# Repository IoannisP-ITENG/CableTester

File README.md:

<div align="center">

# CableTester

<br/>

USB type-C and UTP cable tester designed in faebryk

</div>

## About

This is a simple USB type-C and UTP cable continuity tester. It lights up the LED corresponding to the strand it is testing when there is an electrical connection. The tester is powered with 5V via the PD compliant USB type-C connector.

This project is build with the open-source EDA [faebryk](https://github.com/faebryk/faebryk).

## What can you do with this project?

This project is usefull as a simple cable tester for UTP and USB type-C cables, however it is very easy to add additional connectors for different cable types due to faebryk.

The purpose of this project was mainly to showcase the funcionality of faebryk. The Cable tester is the very first PCBA manufactured from a faebryk design!

### Example

<details>
  <summary>An example of the power of faebryk for PCB design</summary>

</br>

Auto placing components.

```bash
# Generate the netlist with faebryk
python ./source/faebryk/main.py
INFO:__main__:Backup old netlist at ./source/kicad/main/main.net.bak
INFO:__main__:Writing Experiment netlist to ./source/kicad/main/main.net
INFO:__main__:Opening kicad to import new netlist
Import the netlist at ./source/kicad/main/main.net. Press 'Update 
PCB'. Place the components, save the file and exit kicad.

# Let faebryk auto-place your component in a parametric way
INFO:__main__:Writing pcbfile ./source/kicad/main/main.kicad_pcb
```

After importing the generated netlist into KiCad, the layout looks like this:

Let faebryk do the parametric auto placing by using transform functions and coordinates:

```python
# component, rotation
layout_rotation_degrees: List[Tuple[Component, int]] = [
    (pr, 270),
    (mos, 180),
    (clr, 270),
    (led, 0),
]

# left, up, right, down
component_clearances_mm = {
    LED_FP: (2.25, 1, 2, 1),
    RESISTOR_FP: (1, 0.5, 1, 0.5),
    MOSFET_FPS[0]: (2, 3.25, 2, 3.25),
    MOSFET_FPS[1]: (2, 3.25, 2, 3.25),
}
```

And you will get a parametrized PCB layout:

</details>

## Working with the source files

See [here](./docs/development.md) for the instructions on how to install and edit this project.

## Building

If you want to build the physical output of this project you can find the build instructions [here](./docs/build_instructions.md).

## Contributing

If you want to share your alterations, improvements, or add bugfixes to this project, please take a look at the [contributing guidelines](./docs/CONTRIBUTING.md).

## Community Support

Community support is provided via Discord; see the Resources below for details.

### Resources

- Source Code: [Github](https://github.com/IoannisP-ITENG/CableTester)
- Chat: Real-time chat happens in faebryk's Discord Server (chit-chat room for now). Use this Discord [Invite](https://discord.gg/95jYuPmnUW) to register
- Issues: [Issues](https://github.com/IoannisP-ITENG/CableTester/issues)

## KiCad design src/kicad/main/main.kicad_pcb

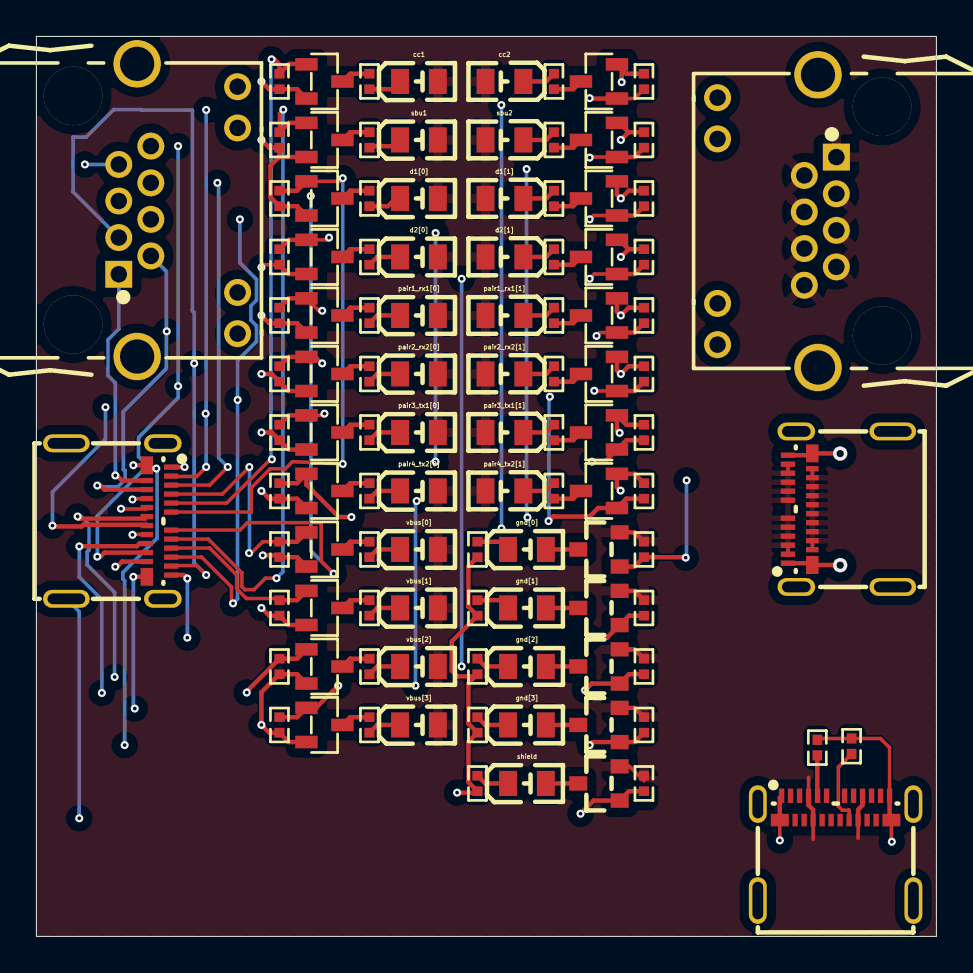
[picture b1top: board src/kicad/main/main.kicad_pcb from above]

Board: 4 copper layers, 50.0 x 50.0 mm, 107 parts (0 on the bottom side), 79 nets.

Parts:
*.psu.configuration_resistors[0][Resistor:5.1kΩ], *.psu.configuration_resistors[1][Resistor:5.1kΩ]: 5.1kΩ; R0402
*.psu.usb[USB_Type_C_Receptacle_24_pin:x], *.tester.usb_c[0][USB_Type_C_Receptacle_24_pin:x], *.tester.usb_c[1][USB_Type_C_Receptacle_24_pin:x]: x; USB-C-SMD_TYPE-C-USB-18
*.tester.cc1.indicator.led.current_limiting_resistor[Resistor:1.0kΩ], *.tester.cc2.indicator.led.current_limiting_resistor[Resistor:1.0kΩ], *.tester.d1[0].indicator.led.current_limiting_resistor[Resistor:1.0kΩ], *.tester.d1[1].indicator.led.current_limiting_resistor[Resistor:1.0kΩ], *.tester.d2[0].indicator.led.current_limiting_resistor[Resistor:1.0kΩ], *.tester.d2[1].indicator.led.current_limiting_resistor[Resistor:1.0kΩ], *.tester.gnd[0].indicator.led.current_limiting_resistor[Resistor:1.0kΩ], *.tester.gnd[1].indicator.led.current_limiting_resistor[Resistor:1.0kΩ], *.tester.gnd[2].indicator.led.current_limiting_resistor[Resistor:1.0kΩ], *.tester.gnd[3].indicator.led.current_limiting_resistor[Resistor:1.0kΩ], *.tester.pair1_rx1[0].indicator.led.current_limiting_resistor[Resistor:1.0kΩ], *.tester.pair1_rx1[1].indicator.led.current_limiting_resistor[Resistor:1.0kΩ], *.tester.pair2_rx2[0].indicator.led.current_limiting_resistor[Resistor:1.0kΩ], *.tester.pair2_rx2[1].indicator.led.current_limiting_resistor[Resistor:1.0kΩ], *.tester.pair3_tx1[0].indicator.led.current_limiting_resistor[Resistor:1.0kΩ], *.tester.pair3_tx1[1].indicator.led.current_limiting_resistor[Resistor:1.0kΩ], *.tester.pair4_tx2[0].indicator.led.current_limiting_resistor[Resistor:1.0kΩ], *.tester.pair4_tx2[1].indicator.led.current_limiting_resistor[Resistor:1.0kΩ], *.tester.sbu1.indicator.led.current_limiting_resistor[Resistor:1.0kΩ], *.tester.sbu2.indicator.led.current_limiting_resistor[Resistor:1.0kΩ], *.tester.shield.indicator.led.current_limiting_resistor[Resistor:1.0kΩ], *.tester.vbus[0].indicator.led.current_limiting_resistor[Resistor:1.0kΩ], *.tester.vbus[1].indicator.led.current_limiting_resistor[Resistor:1.0kΩ], *.tester.vbus[2].indicator.led.current_limiting_resistor[Resistor:1.0kΩ], *.tester.vbus[3].indicator.led.current_limiting_resistor[Resistor:1.0kΩ]: 1.0kΩ; R0402
*.tester.cc1.indicator.led.led[LED:D], *.tester.cc2.indicator.led.led[LED:D], *.tester.d1[0].indicator.led.led[LED:D], *.tester.d1[1].indicator.led.led[LED:D], *.tester.d2[0].indicator.led.led[LED:D], *.tester.d2[1].indicator.led.led[LED:D], *.tester.gnd[0].indicator.led.led[LED:D], *.tester.gnd[1].indicator.led.led[LED:D], *.tester.gnd[2].indicator.led.led[LED:D], *.tester.gnd[3].indicator.led.led[LED:D], *.tester.pair1_rx1[0].indicator.led.led[LED:D], *.tester.pair1_rx1[1].indicator.led.led[LED:D], *.tester.pair2_rx2[0].indicator.led.led[LED:D], *.tester.pair2_rx2[1].indicator.led.led[LED:D], *.tester.pair3_tx1[0].indicator.led.led[LED:D], *.tester.pair3_tx1[1].indicator.led.led[LED:D], *.tester.pair4_tx2[0].indicator.led.led[LED:D], *.tester.pair4_tx2[1].indicator.led.led[LED:D], *.tester.sbu1.indicator.led.led[LED:D], *.tester.sbu2.indicator.led.led[LED:D], *.tester.shield.indicator.led.led[LED:D], *.tester.vbus[0].indicator.led.led[LED:D], *.tester.vbus[1].indicator.led.led[LED:D], *.tester.vbus[2].indicator.led.led[LED:D], *.tester.vbus[3].indicator.led.led[LED:D]: D; LED0805-R-RD
*.tester.cc1.indicator.power_switch.mosfet[MOSFET:Q], *.tester.cc2.indicator.power_switch.mosfet[MOSFET:Q], *.tester.d1[0].indicator.power_switch.mosfet[MOSFET:Q], *.tester.d1[1].indicator.power_switch.mosfet[MOSFET:Q], *.tester.d2[0].indicator.power_switch.mosfet[MOSFET:Q], *.tester.d2[1].indicator.power_switch.mosfet[MOSFET:Q], *.tester.pair1_rx1[0].indicator.power_switch.mosfet[MOSFET:Q], *.tester.pair1_rx1[1].indicator.power_switch.mosfet[MOSFET:Q], *.tester.pair2_rx2[0].indicator.power_switch.mosfet[MOSFET:Q], *.tester.pair2_rx2[1].indicator.power_switch.mosfet[MOSFET:Q], *.tester.pair3_tx1[0].indicator.power_switch.mosfet[MOSFET:Q], *.tester.pair3_tx1[1].indicator.power_switch.mosfet[MOSFET:Q], *.tester.pair4_tx2[0].indicator.power_switch.mosfet[MOSFET:Q], *.tester.pair4_tx2[1].indicator.power_switch.mosfet[MOSFET:Q], *.tester.sbu1.indicator.power_switch.mosfet[MOSFET:Q], *.tester.sbu2.indicator.power_switch.mosfet[MOSFET:Q], *.tester.vbus[0].indicator.power_switch.mosfet[MOSFET:Q], *.tester.vbus[1].indicator.power_switch.mosfet[MOSFET:Q], *.tester.vbus[2].indicator.power_switch.mosfet[MOSFET:Q], *.tester.vbus[3].indicator.power_switch.mosfet[MOSFET:Q]: Q; SOT-23-3_L2.9-W1.3-P1.90-LS2.4-BR
*.tester.cc1.indicator.power_switch.pull_resistor[Resistor:100.0kΩ], *.tester.cc2.indicator.power_switch.pull_resistor[Resistor:100.0kΩ], *.tester.d1[0].indicator.power_switch.pull_resistor[Resistor:100.0kΩ], *.tester.d1[1].indicator.power_switch.pull_resistor[Resistor:100.0kΩ], *.tester.d2[0].indicator.power_switch.pull_resistor[Resistor:100.0kΩ], *.tester.d2[1].indicator.power_switch.pull_resistor[Resistor:100.0kΩ], *.tester.gnd[0].indicator.power_switch.pull_resistor[Resistor:100.0kΩ], *.tester.gnd[1].indicator.power_switch.pull_resistor[Resistor:100.0kΩ], *.tester.gnd[2].indicator.power_switch.pull_resistor[Resistor:100.0kΩ], *.tester.gnd[3].indicator.power_switch.pull_resistor[Resistor:100.0kΩ], *.tester.pair1_rx1[0].indicator.power_switch.pull_resistor[Resistor:100.0kΩ], *.tester.pair1_rx1[1].indicator.power_switch.pull_resistor[Resistor:100.0kΩ], *.tester.pair2_rx2[0].indicator.power_switch.pull_resistor[Resistor:100.0kΩ], *.tester.pair2_rx2[1].indicator.power_switch.pull_resistor[Resistor:100.0kΩ], *.tester.pair3_tx1[0].indicator.power_switch.pull_resistor[Resistor:100.0kΩ], *.tester.pair3_tx1[1].indicator.power_switch.pull_resistor[Resistor:100.0kΩ], *.tester.pair4_tx2[0].indicator.power_switch.pull_resistor[Resistor:100.0kΩ], *.tester.pair4_tx2[1].indicator.power_switch.pull_resistor[Resistor:100.0kΩ], *.tester.sbu1.indicator.power_switch.pull_resistor[Resistor:100.0kΩ], *.tester.sbu2.indicator.power_switch.pull_resistor[Resistor:100.0kΩ], *.tester.shield.indicator.power_switch.pull_resistor[Resistor:100.0kΩ], *.tester.vbus[0].indicator.power_switch.pull_resistor[Resistor:100.0kΩ], *.tester.vbus[1].indicator.power_switch.pull_resistor[Resistor:100.0kΩ], *.tester.vbus[2].indicator.power_switch.pull_resistor[Resistor:100.0kΩ], *.tester.vbus[3].indicator.power_switch.pull_resistor[Resistor:100.0kΩ]: 100.0kΩ; R0402
*.tester.gnd[0].indicator.power_switch.mosfet[MOSFET:Q], *.tester.gnd[1].indicator.power_switch.mosfet[MOSFET:Q], *.tester.gnd[2].indicator.power_switch.mosfet[MOSFET:Q], *.tester.gnd[3].indicator.power_switch.mosfet[MOSFET:Q], *.tester.shield.indicator.power_switch.mosfet[MOSFET:Q]: Q; SOT-23_L2.9-W1.3-P1.90-LS2.4-BR
*.tester.rj45[0][RJ45_Receptacle:x], *.tester.rj45[1][RJ45_Receptacle:x]: x; RJ45-TH_B-1-1

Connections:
*.psu.usb[USB_Type_C_Receptacle_24_pin:x]-psu.configuration_resistors[0][Resist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: *.psu.configuration_resistors[0][Resist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.1, *.psu.usb[USB_Type_C_Receptacle_24_pin: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.A5
*.psu.usb[USB_Type_C_Receptacle_24_pin:x]-psu.configuration_resistors[1][Resist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: *.psu.configuration_resistors[1][Resist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.1, *.psu.usb[USB_Type_C_Receptacle_24_pin: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.B5
*.tester.cc1.indicator.led.current_limiting_resistor[Resistor:1.0kΩ]-*.tester.c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: *.tester.cc1.indicator.led.current_limi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.2, *.tester.cc1.indicator.led.led[LED:D].2
*.tester.cc1.indicator.power_switch[PowerSwitch:virt]:5-*.tester.cc1.indicator.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: *.tester.cc1.indicator.led.current_limi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.1, *.tester.cc1.indicator.power_switch.mos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.3
*.tester.cc1.indicator[LEDIndicator:virt]-*.tester.cc1.indicator.power_switch[P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: *.tester.cc1.indicator.power_switch.mos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.1, *.tester.cc1.indicator.power_switch.pul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.1, *.tester.usb_c[1][USB_Type_C_Receptacle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.A5
*.tester.cc2.indicator.led.led[LED:D]-*.tester.cc2.indicator.led.current_limiti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: *.tester.cc2.indicator.led.current_limi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.2, *.tester.cc2.indicator.led.led[LED:D].2
*.tester.cc2.indicator.power_switch[PowerSwitch:virt]-*.tester.cc2.indicator[LE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: *.tester.cc2.indicator.power_switch.mos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.1, *.tester.cc2.indicator.power_switch.pul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.1, *.tester.usb_c[1][USB_Type_C_Receptacle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.B5
*.tester.cc2.indicator.power_switch[PowerSwitch:virt]:5-*.tester.cc2.indicator.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: *.tester.cc2.indicator.led.current_limi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.1, *.tester.cc2.indicator.power_switch.mos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.3
*.tester.d1[0].indicator.led.current_limiting_resistor[Resistor:1.0kΩ]-*.tester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: *.tester.d1[0].indicator.led.current_li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.2, *.tester.d1[0].indicator.led.led[LED:D].2
*.tester.d1[0].indicator.led[PoweredLED:virt]:2-*.tester.d1[0].indicator.power_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: *.tester.d1[0].indicator.led.current_li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.1, *.tester.d1[0].indicator.power_switch.m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.3
*.tester.d1[0].indicator[LEDIndicator:virt]-*.tester.d1[0].indicator.power_swit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: *.tester.d1[0].indicator.power_switch.m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.1, *.tester.d1[0].indicator.power_switch.p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.1, *.tester.usb_c[1][USB_Type_C_Receptacle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.A6
*.tester.d1[1].indicator.led.led[LED:D]-*.tester.d1[1].indicator.led.current_li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: *.tester.d1[1].indicator.led.current_li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.2, *.tester.d1[1].indicator.led.led[LED:D].2
*.tester.d1[1].indicator.power_switch[PowerSwitch:virt]-*.tester.d1[1][Pair*.te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: *.tester.d1[1].indicator.power_switch.m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.1, *.tester.d1[1].indicator.power_switch.p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.1, *.tester.usb_c[1][USB_Type_C_Receptacle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.A7
*.tester.d1[1].indicator.power_switch[PowerSwitch:virt]:5-*.tester.d1[1].indica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: *.tester.d1[1].indicator.led.current_li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.1, *.tester.d1[1].indicator.power_switch.m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.3
*.tester.d2[0].indicator.led.current_limiting_resistor[Resistor:1.0kΩ]-*.tester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: *.tester.d2[0].indicator.led.current_li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.2, *.tester.d2[0].indicator.led.led[LED:D].2
*.tester.d2[0].indicator.power_switch[PowerSwitch:virt]:5-*.tester.d2[0].indica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: *.tester.d2[0].indicator.led.current_li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.1, *.tester.d2[0].indicator.power_switch.m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.3
*.tester.d2[0][Pair*.tester:virt]:4-*.tester.d2[0].indicator.power_switch[Power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: *.tester.d2[0].indicator.power_switch.m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.1, *.tester.d2[0].indicator.power_switch.p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.1, *.tester.usb_c[1][USB_Type_C_Receptacle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.B6
*.tester.d2[1].indicator.led.current_limiting_resistor[Resistor:1.0kΩ]-*.tester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: *.tester.d2[1].indicator.led.current_li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.2, *.tester.d2[1].indicator.led.led[LED:D].2
*.tester.d2[1].indicator.power_switch[PowerSwitch:virt]:5-*.tester.d2[1].indica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: *.tester.d2[1].indicator.led.current_li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.1, *.tester.d2[1].indicator.power_switch.m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.3
*.tester.d2[1][Pair*.tester:virt]:4-*.tester.d2[1].indicator[LEDIndicator:virt]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: *.tester.d2[1].indicator.power_switch.m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.1, *.tester.d2[1].indicator.power_switch.p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.1, *.tester.usb_c[1][USB_Type_C_Receptacle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.B7
*.tester.gnd[0].indicator.led.led[LED:D]-*.tester.gnd[0].indicator.led.current_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: *.tester.gnd[0].indicator.led.current_l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.2, *.tester.gnd[0].indicator.led.led[LED:D].2
*.tester.gnd[0].indicator.power_switch[PowerSwitch:virt]-*.tester.gnd[0].indica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: *.tester.gnd[0].indicator.power_switch.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.1, *.tester.gnd[0].indicator.power_switch.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.1, *.tester.usb_c[1][USB_Type_C_Receptacle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.A1
*.tester.gnd[0].indicator.power_switch[PowerSwitch:virt]:4-*.tester.gnd[0].indi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: *.tester.gnd[0].indicator.led.led[LED:D].1, *.tester.gnd[0].indicator.power_switch.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.3
*.tester.gnd[1].indicator.led.led[LED:D]-*.tester.gnd[1].indicator.led.current_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: *.tester.gnd[1].indicator.led.current_l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.2, *.tester.gnd[1].indicator.led.led[LED:D].2
*.tester.gnd[1].indicator.power_switch[PowerSwitch:virt]:4-*.tester.gnd[1].indi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: *.tester.gnd[1].indicator.led.led[LED:D].1, *.tester.gnd[1].indicator.power_switch.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.3
*.tester.gnd[1][Pair*.tester:virt]:4-*.tester.gnd[1].indicator.power_switch[Pow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: *.tester.gnd[1].indicator.power_switch.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.1, *.tester.gnd[1].indicator.power_switch.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.1, *.tester.usb_c[1][USB_Type_C_Receptacle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.A12
*.tester.gnd[2].indicator.led.led[LED:D]-*.tester.gnd[2].indicator.led.current_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: *.tester.gnd[2].indicator.led.current_l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.2, *.tester.gnd[2].indicator.led.led[LED:D].2
*.tester.gnd[2].indicator.led[PoweredLED:virt]-*.tester.gnd[2].indicator.power_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: *.tester.gnd[2].indicator.led.led[LED:D].1, *.tester.gnd[2].indicator.power_switch.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.3
*.tester.gnd[2][Pair*.tester:virt]:4-*.tester.gnd[2].indicator[LEDIndicator:vir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: *.tester.gnd[2].indicator.power_switch.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.1, *.tester.gnd[2].indicator.power_switch.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.1, *.tester.usb_c[1][USB_Type_C_Receptacle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.B1
*.tester.gnd[3].indicator.led.led[LED:D]-*.tester.gnd[3].indicator.led.current_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: *.tester.gnd[3].indicator.led.current_l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.2, *.tester.gnd[3].indicator.led.led[LED:D].2
*.tester.gnd[3].indicator.led[PoweredLED:virt]-*.tester.gnd[3].indicator.power_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: *.tester.gnd[3].indicator.led.led[LED:D].1, *.tester.gnd[3].indicator.power_switch.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.3
*.tester.gnd[3][Pair*.tester:virt]:4-*.tester.gnd[3].indicator[LEDIndicator:vir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: *.tester.gnd[3].indicator.power_switch.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.1, *.tester.gnd[3].indicator.power_switch.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.1, *.tester.usb_c[1][USB_Type_C_Receptacle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.B12
*.tester.pair1_rx1[0].indicator.led.led[LED:D]-*.tester.pair1_rx1[0].indicator.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: *.tester.pair1_rx1[0].indicator.led.cur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.2, *.tester.pair1_rx1[0].indicator.led.led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.2
*.tester.pair1_rx1[0].indicator.led[PoweredLED:virt]:2-*.tester.pair1_rx1[0].in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: *.tester.pair1_rx1[0].indicator.led.cur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.1, *.tester.pair1_rx1[0].indicator.power_s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.3
*.tester.pair1_rx1[0][Pair*.tester:virt]:4-*.tester.pair1_rx1[0].indicator.powe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: *.tester.pair1_rx1[0].indicator.power_s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.1, *.tester.pair1_rx1[0].indicator.power_s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.1, *.tester.rj45[1][RJ45_Receptacle:x].1, *.tester.usb_c[1][USB_Type_C_Receptacle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.B11
*.tester.pair1_rx1[1].indicator.led.current_limiting_resistor[Resistor:1.0kΩ]-*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: *.tester.pair1_rx1[1].indicator.led.cur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.2, *.tester.pair1_rx1[1].indicator.led.led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.2
*.tester.pair1_rx1[1].indicator.led[PoweredLED:virt]-*.tester.d2[1].indicator.p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: *.psu.usb[USB_Type_C_Receptacle_24_pin: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.A4, *.psu.usb[USB_Type_C_Receptacle_24_pin: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.A9, *.psu.usb[USB_Type_C_Receptacle_24_pin: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.B4, *.psu.usb[USB_Type_C_Receptacle_24_pin: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.B9, *.tester.cc1.indicator.led.led[LED:D].1, *.tester.cc2.indicator.led.led[LED:D].1, *.tester.d1[0].indicator.led.led[LED:D].1, *.tester.d1[1].indicator.led.led[LED:D].1, *.tester.d2[0].indicator.led.led[LED:D].1, *.tester.d2[1].indicator.led.led[LED:D].1, *.tester.gnd[0].indicator.power_switch.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.2, *.tester.gnd[0].indicator.power_switch.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.2, *.tester.gnd[1].indicator.power_switch.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.2, *.tester.gnd[1].indicator.power_switch.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.2, *.tester.gnd[2].indicator.power_switch.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.2, *.tester.gnd[2].indicator.power_switch.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.2, *.tester.gnd[3].indicator.power_switch.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.2, *.tester.gnd[3].indicator.power_switch.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.2, *.tester.pair1_rx1[0].indicator.led.led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.1, *.tester.pair1_rx1[1].indicator.led.led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.1, *.tester.pair2_rx2[0].indicator.led.led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.1, *.tester.pair2_rx2[1].indicator.led.led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.1, *.tester.pair3_tx1[0].indicator.led.led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.1, *.tester.pair3_tx1[1].indicator.led.led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.1, *.tester.pair4_tx2[0].indicator.led.led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.1, *.tester.pair4_tx2[1].indicator.led.led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.1, *.tester.rj45[0][RJ45_Receptacle:x].1, *.tester.rj45[0][RJ45_Receptacle:x].2, *.tester.rj45[0][RJ45_Receptacle:x].3, *.tester.rj45[0][RJ45_Receptacle:x].4, *.tester.rj45[0][RJ45_Receptacle:x].5, *.tester.rj45[0][RJ45_Receptacle:x].6, *.tester.rj45[0][RJ45_Receptacle:x].7, *.tester.rj45[0][RJ45_Receptacle:x].8, *.tester.sbu1.indicator.led.led[LED:D].1, *.tester.sbu2.indicator.led.led[LED:D].1, *.tester.shield.indicator.power_switch.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.2, *.tester.shield.indicator.power_switch.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.2, *.tester.usb_c[0][USB_Type_C_Receptacle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.A2, *.tester.usb_c[0][USB_Type_C_Receptacle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.A3, *.tester.usb_c[0][USB_Type_C_Receptacle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.A4, *.tester.usb_c[0][USB_Type_C_Receptacle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.A5, *.tester.usb_c[0][USB_Type_C_Receptacle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.A6, *.tester.usb_c[0][USB_Type_C_Receptacle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.A7, *.tester.usb_c[0][USB_Type_C_Receptacle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.A8, *.tester.usb_c[0][USB_Type_C_Receptacle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.A9, *.tester.usb_c[0][USB_Type_C_Receptacle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.A10, *.tester.usb_c[0][USB_Type_C_Receptacle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.A11, *.tester.usb_c[0][USB_Type_C_Receptacle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.B2, *.tester.usb_c[0][USB_Type_C_Receptacle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.B3, *.tester.usb_c[0][USB_Type_C_Receptacle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.B4, *.tester.usb_c[0][USB_Type_C_Receptacle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.B5, *.tester.usb_c[0][USB_Type_C_Receptacle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.B6, *.tester.usb_c[0][USB_Type_C_Receptacle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.B7, *.tester.usb_c[0][USB_Type_C_Receptacle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.B8, *.tester.usb_c[0][USB_Type_C_Receptacle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.B9, *.tester.usb_c[0][USB_Type_C_Receptacle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.B10, *.tester.usb_c[0][USB_Type_C_Receptacle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.B11, *.tester.vbus[0].indicator.led.led[LED: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.1, *.tester.vbus[1].indicator.led.led[LED: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.1, *.tester.vbus[2].indicator.led.led[LED: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.1, *.tester.vbus[3].indicator.led.led[LED: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.1
*.tester.pair1_rx1[1].indicator.power_switch[PowerSwitch:virt]:5-*.tester.pair1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: *.tester.pair1_rx1[1].indicator.led.cur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.1, *.tester.pair1_rx1[1].indicator.power_s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.3
*.tester.pair1_rx1[1][Pair*.tester:virt]:4-*.tester.pair1_rx1[1].indicator[LEDI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: *.tester.pair1_rx1[1].indicator.power_s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.1, *.tester.pair1_rx1[1].indicator.power_s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.1, *.tester.rj45[1][RJ45_Receptacle:x].2, *.tester.usb_c[1][USB_Type_C_Receptacle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.B10
*.tester.pair2_rx2[0].indicator.led.led[LED:D]-*.tester.pair2_rx2[0].indicator.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: *.tester.pair2_rx2[0].indicator.led.cur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.2, *.tester.pair2_rx2[0].indicator.led.led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.2
*.tester.pair2_rx2[0].indicator.power_switch[PowerSwitch:virt]:5-*.tester.pair2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: *.tester.pair2_rx2[0].indicator.led.cur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.1, *.tester.pair2_rx2[0].indicator.power_s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.3
*.tester.pair2_rx2[0].indicator[LEDIndicator:virt]-*.tester.pair2_rx2[0][Pair*.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: *.tester.pair2_rx2[0].indicator.power_s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.1, *.tester.pair2_rx2[0].indicator.power_s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.1, *.tester.rj45[1][RJ45_Receptacle:x].3, *.tester.usb_c[1][USB_Type_C_Receptacle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.A11
*.tester.pair2_rx2[1].indicator.led.current_limiting_resistor[Resistor:1.0kΩ]-*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: *.tester.pair2_rx2[1].indicator.led.cur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.2, *.tester.pair2_rx2[1].indicator.led.led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.2
*.tester.pair2_rx2[1].indicator.power_switch[PowerSwitch:virt]-*.tester.pair2_r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: *.tester.pair2_rx2[1].indicator.power_s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.1, *.tester.pair2_rx2[1].indicator.power_s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.1, *.tester.rj45[1][RJ45_Receptacle:x].4, *.tester.usb_c[1][USB_Type_C_Receptacle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.A10
*.tester.pair2_rx2[1].indicator.power_switch[PowerSwitch:virt]:5-*.tester.pair2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: *.tester.pair2_rx2[1].indicator.led.cur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.1, *.tester.pair2_rx2[1].indicator.power_s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.3
*.tester.pair3_tx1[0].indicator.led.current_limiting_resistor[Resistor:1.0kΩ]-*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: *.tester.pair3_tx1[0].indicator.led.cur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.2, *.tester.pair3_tx1[0].indicator.led.led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.2
*.tester.pair3_tx1[0].indicator.power_switch[PowerSwitch:virt]-*.tester.pair3_t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: *.tester.pair3_tx1[0].indicator.power_s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.1, *.tester.pair3_tx1[0].indicator.power_s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.1, *.tester.rj45[1][RJ45_Receptacle:x].5, *.tester.usb_c[1][USB_Type_C_Receptacle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.A2
*.tester.pair3_tx1[0].indicator.power_switch[PowerSwitch:virt]:5-*.tester.pair3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: *.tester.pair3_tx1[0].indicator.led.cur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.1, *.tester.pair3_tx1[0].indicator.power_s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.3
*.tester.pair3_tx1[1].indicator.led.current_limiting_resistor[Resistor:1.0kΩ]-*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: *.tester.pair3_tx1[1].indicator.led.cur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.2, *.tester.pair3_tx1[1].indicator.led.led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.2
*.tester.pair3_tx1[1].indicator.power_switch[PowerSwitch:virt]:5-*.tester.pair3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: *.tester.pair3_tx1[1].indicator.led.cur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.1, *.tester.pair3_tx1[1].indicator.power_s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.3
*.tester.pair3_tx1[1].indicator[LEDIndicator:virt]-*.tester.pair3_tx1[1][Pair*.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: *.tester.pair3_tx1[1].indicator.power_s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.1, *.tester.pair3_tx1[1].indicator.power_s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.1, *.tester.rj45[1][RJ45_Receptacle:x].6, *.tester.usb_c[1][USB_Type_C_Receptacle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.A3
*.tester.pair4_tx2[0].indicator.led.led[LED:D]-*.tester.pair4_tx2[0].indicator.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: *.tester.pair4_tx2[0].indicator.led.cur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.2, *.tester.pair4_tx2[0].indicator.led.led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.2
*.tester.pair4_tx2[0].indicator.power_switch[PowerSwitch:virt]:5-*.tester.pair4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: *.tester.pair4_tx2[0].indicator.led.cur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.1, *.tester.pair4_tx2[0].indicator.power_s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.3
*.tester.pair4_tx2[0].indicator[LEDIndicator:virt]-*.tester.pair4_tx2[0].indica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: *.tester.pair4_tx2[0].indicator.power_s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.1, *.tester.pair4_tx2[0].indicator.power_s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.1, *.tester.rj45[1][RJ45_Receptacle:x].7, *.tester.usb_c[1][USB_Type_C_Receptacle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.B2
*.tester.pair4_tx2[1].indicator.led.led[LED:D]-*.tester.pair4_tx2[1].indicator.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: *.tester.pair4_tx2[1].indicator.led.cur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.2, *.tester.pair4_tx2[1].indicator.led.led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.2
*.tester.pair4_tx2[1].indicator.power_switch[PowerSwitch:virt]:5-*.tester.pair4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: *.tester.pair4_tx2[1].indicator.led.cur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.1, *.tester.pair4_tx2[1].indicator.power_s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.3
*.tester.pair4_tx2[1].indicator[LEDIndicator:virt]-*.tester.pair4_tx2[1].indica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: *.tester.pair4_tx2[1].indicator.power_s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.1, *.tester.pair4_tx2[1].indicator.power_s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.1, *.tester.rj45[1][RJ45_Receptacle:x].8, *.tester.usb_c[1][USB_Type_C_Receptacle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.B3
*.tester.sbu1.indicator.led.led[LED:D]-*.tester.sbu1.indicator.led.current_limi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: *.tester.sbu1.indicator.led.current_lim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.2, *.tester.sbu1.indicator.led.led[LED:D].2
*.tester.sbu1.indicator.led[PoweredLED:virt]:2-*.tester.sbu1.indicator.power_sw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: *.tester.sbu1.indicator.led.current_lim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.1, *.tester.sbu1.indicator.power_switch.mo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.3
*.tester.sbu1.indicator[LEDIndicator:virt]-*.tester.sbu1.indicator.power_switch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: *.tester.sbu1.indicator.power_switch.mo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.1, *.tester.sbu1.indicator.power_switch.pu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.1, *.tester.usb_c[1][USB_Type_C_Receptacle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.A8
*.tester.sbu2.indicator.led.led[LED:D]-*.tester.sbu2.indicator.led.current_limi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: *.tester.sbu2.indicator.led.current_lim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.2, *.tester.sbu2.indicator.led.led[LED:D].2
*.tester.sbu2.indicator.power_switch[PowerSwitch:virt]-*.tester.sbu2[Pair*.test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: *.tester.sbu2.indicator.power_switch.mo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.1, *.tester.sbu2.indicator.power_switch.pu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.1, *.tester.usb_c[1][USB_Type_C_Receptacle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.B8
*.tester.sbu2.indicator.power_switch[PowerSwitch:virt]:5-*.tester.sbu2.indicato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: *.tester.sbu2.indicator.led.current_lim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.1, *.tester.sbu2.indicator.power_switch.mo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.3
*.tester.shield.indicator.led.led[LED:D]-*.tester.shield.indicator.led.current_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: *.tester.shield.indicator.led.current_l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.2, *.tester.shield.indicator.led.led[LED:D].2
*.tester.shield.indicator.led[PoweredLED:virt]-*.tester.shield.indicator.power_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: *.tester.shield.indicator.led.led[LED:D].1, *.tester.shield.indicator.power_switch.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.3
*.tester.shield.indicator.power_switch[PowerSwitch:virt]-*.tester.shield.indica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: *.tester.shield.indicator.power_switch.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.1, *.tester.shield.indicator.power_switch.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.1, *.tester.usb_c[1][USB_Type_C_Receptacle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.0
*.tester.vbus[0].indicator.led.led[LED:D]-*.tester.vbus[0].indicator.led.curren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: *.tester.vbus[0].indicator.led.current_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.2, *.tester.vbus[0].indicator.led.led[LED: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.2
*.tester.vbus[0].indicator.led[PoweredLED:virt]:2-*.tester.vbus[0].indicator.po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: *.tester.vbus[0].indicator.led.current_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.1, *.tester.vbus[0].indicator.power_switch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.3
*.tester.vbus[0][Pair*.tester:virt]:4-*.tester.vbus[0].indicator[LEDIndicator:v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: *.tester.usb_c[1][USB_Type_C_Receptacle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.A4, *.tester.vbus[0].indicator.power_switch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.1, *.tester.vbus[0].indicator.power_switch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.1
*.tester.vbus[1].indicator.led.led[LED:D]-*.tester.vbus[1].indicator.led.curren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: *.tester.vbus[1].indicator.led.current_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.2, *.tester.vbus[1].indicator.led.led[LED: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.2
*.tester.vbus[1].indicator.power_switch[PowerSwitch:virt]:5-*.tester.vbus[1].in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: *.tester.vbus[1].indicator.led.current_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.1, *.tester.vbus[1].indicator.power_switch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.3
*.tester.vbus[1].indicator[LEDIndicator:virt]:3-*.tester.shield.indicator[LEDIn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: *.psu.configuration_resistors[0][Resist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.2, *.psu.configuration_resistors[1][Resist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.2, *.psu.usb[USB_Type_C_Receptacle_24_pin: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.A1, *.psu.usb[USB_Type_C_Receptacle_24_pin: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.A12, *.psu.usb[USB_Type_C_Receptacle_24_pin: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.B1, *.psu.usb[USB_Type_C_Receptacle_24_pin: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.B12, *.tester.cc1.indicator.power_switch.mos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.2, *.tester.cc1.indicator.power_switch.pul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.2, *.tester.cc2.indicator.power_switch.mos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.2, *.tester.cc2.indicator.power_switch.pul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.2, *.tester.d1[0].indicator.power_switch.m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.2, *.tester.d1[0].indicator.power_switch.p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.2, *.tester.d1[1].indicator.power_switch.m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.2, *.tester.d1[1].indicator.power_switch.p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.2, *.tester.d2[0].indicator.power_switch.m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.2, *.tester.d2[0].indicator.power_switch.p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.2, *.tester.d2[1].indicator.power_switch.m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.2, *.tester.d2[1].indicator.power_switch.p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.2, *.tester.gnd[0].indicator.led.current_l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.1, *.tester.gnd[1].indicator.led.current_l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.1, *.tester.gnd[2].indicator.led.current_l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.1, *.tester.gnd[3].indicator.led.current_l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.1, *.tester.pair1_rx1[0].indicator.power_s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.2, *.tester.pair1_rx1[0].indicator.power_s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.2, *.tester.pair1_rx1[1].indicator.power_s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.2, *.tester.pair1_rx1[1].indicator.power_s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.2, *.tester.pair2_rx2[0].indicator.power_s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.2, *.tester.pair2_rx2[0].indicator.power_s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.2, *.tester.pair2_rx2[1].indicator.power_s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.2, *.tester.pair2_rx2[1].indicator.power_s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.2, *.tester.pair3_tx1[0].indicator.power_s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.2, *.tester.pair3_tx1[0].indicator.power_s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.2, *.tester.pair3_tx1[1].indicator.power_s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.2, *.tester.pair3_tx1[1].indicator.power_s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.2, *.tester.pair4_tx2[0].indicator.power_s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.2, *.tester.pair4_tx2[0].indicator.power_s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.2, *.tester.pair4_tx2[1].indicator.power_s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.2, *.tester.pair4_tx2[1].indicator.power_s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.2, *.tester.sbu1.indicator.power_switch.mo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.2, *.tester.sbu1.indicator.power_switch.pu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.2, *.tester.sbu2.indicator.power_switch.mo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.2, *.tester.sbu2.indicator.power_switch.pu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.2, *.tester.shield.indicator.led.current_l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.1, *.tester.usb_c[0][USB_Type_C_Receptacle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.0, *.tester.usb_c[0][USB_Type_C_Receptacle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.A1, *.tester.usb_c[0][USB_Type_C_Receptacle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.A12, *.tester.usb_c[0][USB_Type_C_Receptacle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.B1, *.tester.usb_c[0][USB_Type_C_Receptacle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.B12, *.tester.vbus[0].indicator.power_switch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.2, *.tester.vbus[0].indicator.power_switch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.2, *.tester.vbus[1].indicator.power_switch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.2, *.tester.vbus[1].indicator.power_switch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.2, *.tester.vbus[2].indicator.power_switch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.2, *.tester.vbus[2].indicator.power_switch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.2, *.tester.vbus[3].indicator.power_switch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.2, *.tester.vbus[3].indicator.power_switch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.2
*.tester.vbus[1][Pair*.tester:virt]:4-*.tester.vbus[1].indicator.power_switch[P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: *.tester.usb_c[1][USB_Type_C_Receptacle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.A9, *.tester.vbus[1].indicator.power_switch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.1, *.tester.vbus[1].indicator.power_switch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.1
*.tester.vbus[2].indicator.led.led[LED:D]-*.tester.vbus[2].indicator.led.curren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: *.tester.vbus[2].indicator.led.current_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.2, *.tester.vbus[2].indicator.led.led[LED: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.2
*.tester.vbus[2].indicator.led[PoweredLED:virt]:2-*.tester.vbus[2].indicator.po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: *.tester.vbus[2].indicator.led.current_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.1, *.tester.vbus[2].indicator.power_switch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.3
*.tester.vbus[2][Pair*.tester:virt]:4-*.tester.vbus[2].indicator[LEDIndicator:v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: *.tester.usb_c[1][USB_Type_C_Receptacle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.B4, *.tester.vbus[2].indicator.power_switch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.1, *.tester.vbus[2].indicator.power_switch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.1
*.tester.vbus[3].indicator.led.current_limiting_resistor[Resistor:1.0kΩ]-*.test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: *.tester.vbus[3].indicator.led.current_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.2, *.tester.vbus[3].indicator.led.led[LED: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.2
*.tester.vbus[3].indicator.power_switch[PowerSwitch:virt]:5-*.tester.vbus[3].in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: *.tester.vbus[3].indicator.led.current_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.1, *.tester.vbus[3].indicator.power_switch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.3
*.tester.vbus[3][Pair*.tester:virt]:4-*.tester.vbus[3].indicator.power_switch[P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: *.tester.usb_c[1][USB_Type_C_Receptacle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.B9, *.tester.vbus[3].indicator.power_switch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.1, *.tester.vbus[3].indicator.power_switch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.1

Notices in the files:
README.md:
License: MIT
